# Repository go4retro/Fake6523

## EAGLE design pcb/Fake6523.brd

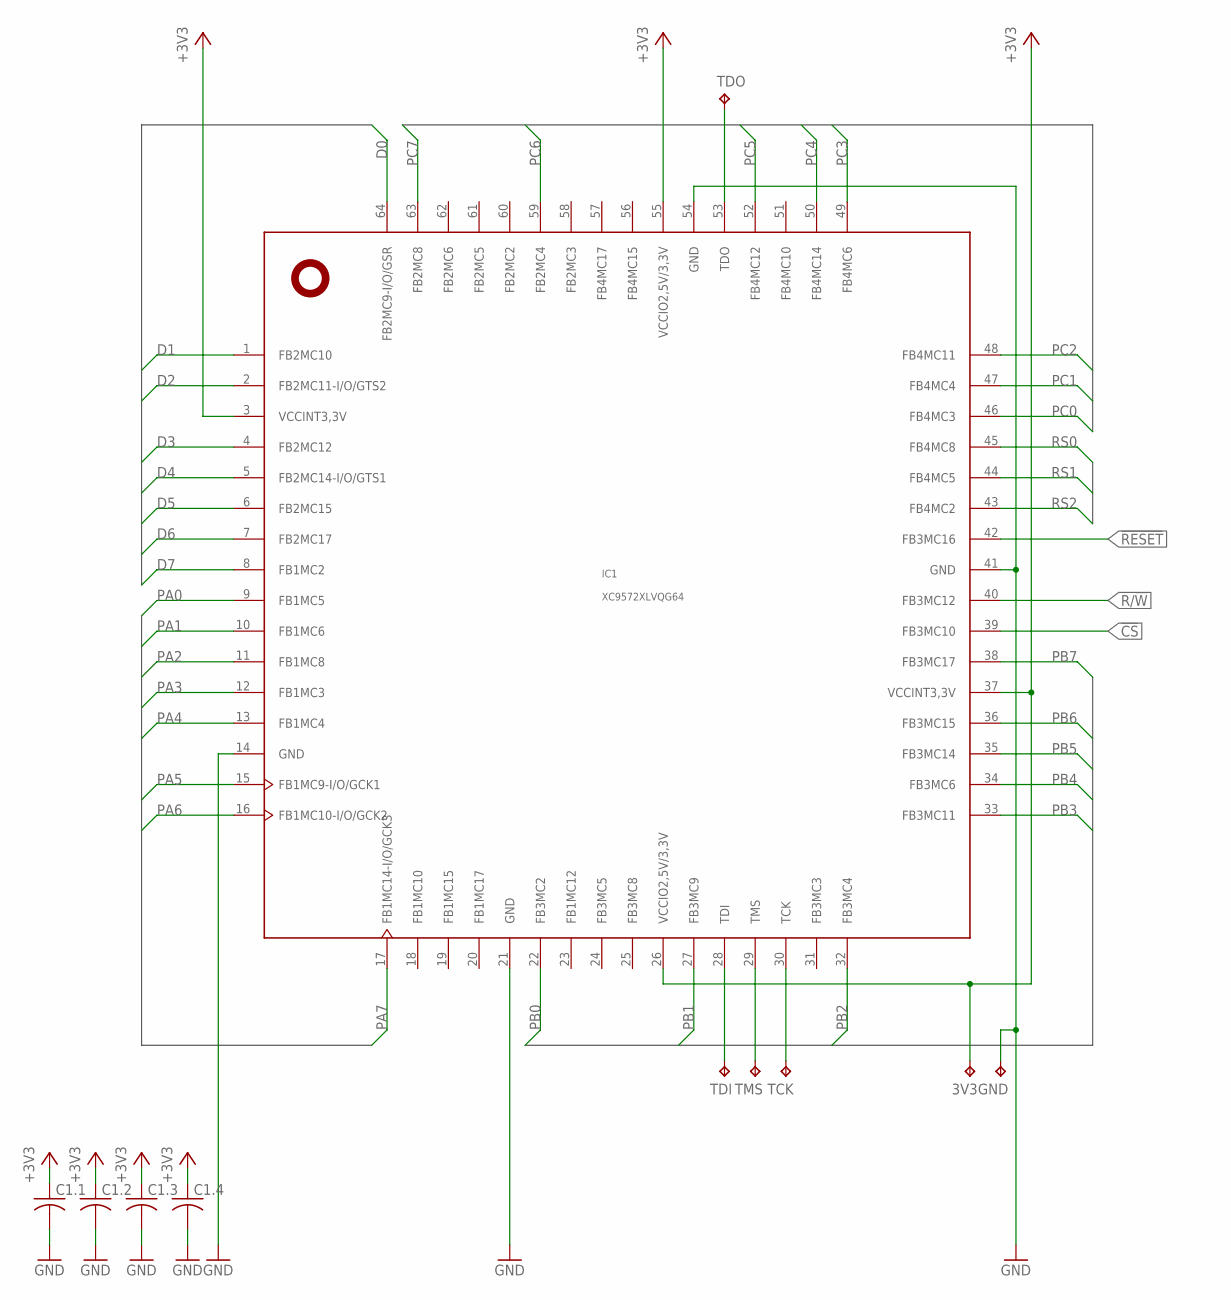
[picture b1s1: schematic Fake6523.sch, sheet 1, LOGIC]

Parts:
3V3: TPTP08R; TP08R
C1.1, C1.2, C1.3, C1.4: C-USC0402; C0402
GND: TPTP08R; TP08R
IC1: XC9572XLVQG64; VQFP64
TCK: TPTP08R; TP08R
TDI: TPTP08R; TP08R
TDO: TPTP08R; TP08R
TMS: TPTP08R; TP08R

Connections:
!CS: IC1.39 (FB3MC10); also elsewhere on the board
!RESET: IC1.42 (FB3MC16); also elsewhere on the board
+3V3: 3V3.TP, C1.1.1, C1.2.1, C1.3.1, C1.4.1, IC1.3 (VCCINT3,3V), IC1.26 (VCCIO2,5V/3,3V), IC1.37 (VCCINT3,3V), IC1.55 (VCCIO2,5V/3,3V); also elsewhere on the board
D0: IC1.64 (FB2MC9-I/O/GSR); also elsewhere on the board
D1: IC1.1 (FB2MC10); also elsewhere on the board
D2: IC1.2 (FB2MC11-I/O/GTS2); also elsewhere on the board
D3: IC1.4 (FB2MC12); also elsewhere on the board
D4: IC1.5 (FB2MC14-I/O/GTS1); also elsewhere on the board
D5: IC1.6 (FB2MC15); also elsewhere on the board
D6: IC1.7 (FB2MC17); also elsewhere on the board
D7: IC1.8 (FB1MC2); also elsewhere on the board
GND: C1.1.2, C1.2.2, C1.3.2, C1.4.2, GND.TP, IC1.14 (GND), IC1.21 (GND), IC1.41 (GND), IC1.54 (GND); also elsewhere on the board
PA0: IC1.9 (FB1MC5); also elsewhere on the board
PA1: IC1.10 (FB1MC6); also elsewhere on the board
PA2: IC1.11 (FB1MC8); also elsewhere on the board
PA3: IC1.12 (FB1MC3); also elsewhere on the board
PA4: IC1.13 (FB1MC4); also elsewhere on the board
PA5: IC1.15 (FB1MC9-I/O/GCK1); also elsewhere on the board
PA6: IC1.16 (FB1MC10-I/O/GCK2); also elsewhere on the board
PA7: IC1.17 (FB1MC14-I/O/GCK3); also elsewhere on the board
PB0: IC1.22 (FB3MC2); also elsewhere on the board
PB1: IC1.27 (FB3MC9); also elsewhere on the board
PB2: IC1.32 (FB3MC4); also elsewhere on the board
PB3: IC1.33 (FB3MC11); also elsewhere on the board
PB4: IC1.34 (FB3MC6); also elsewhere on the board
PB5: IC1.35 (FB3MC14); also elsewhere on the board
PB6: IC1.36 (FB3MC15); also elsewhere on the board
PB7: IC1.38 (FB3MC17); also elsewhere on the board
PC0: IC1.46 (FB4MC3); also elsewhere on the board
PC1: IC1.47 (FB4MC4); also elsewhere on the board
PC2: IC1.48 (FB4MC11); also elsewhere on the board
PC3: IC1.49 (FB4MC6); also elsewhere on the board
PC4: IC1.50 (FB4MC14); also elsewhere on the board
PC5: IC1.52 (FB4MC12); also elsewhere on the board
PC6: IC1.59 (FB2MC4); also elsewhere on the board
PC7: IC1.63 (FB2MC8); also elsewhere on the board
R/!W: IC1.40 (FB3MC12); also elsewhere on the board
RS0: IC1.45 (FB4MC8); also elsewhere on the board
RS1: IC1.44 (FB4MC5); also elsewhere on the board
RS2: IC1.43 (FB4MC2); also elsewhere on the board
TCK: IC1.30 (TCK), TCK.TP
TDI: IC1.28 (TDI), TDI.TP
TDO: IC1.53 (TDO), TDO.TP
TMS: IC1.29 (TMS), TMS.TP

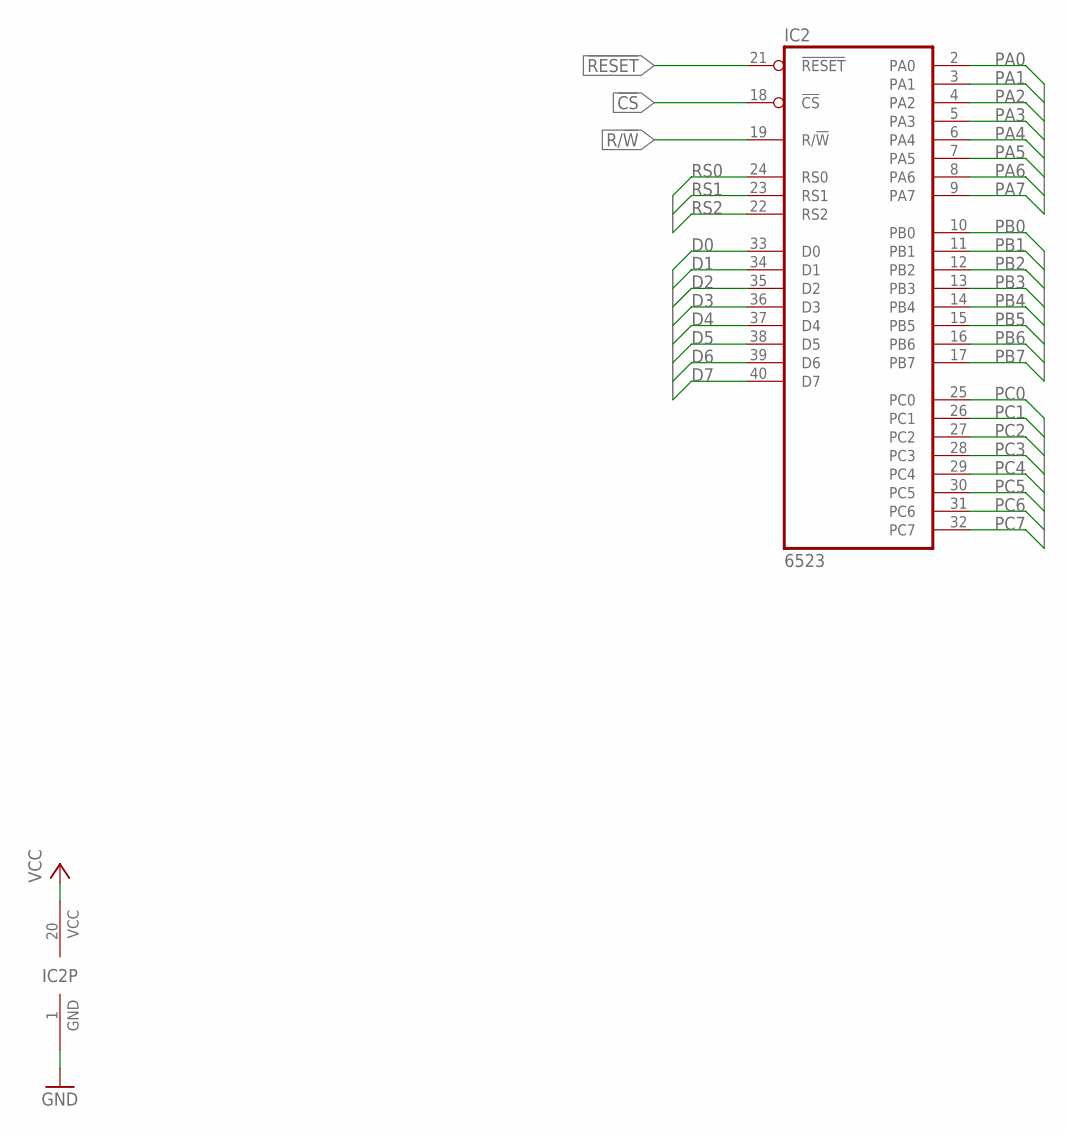
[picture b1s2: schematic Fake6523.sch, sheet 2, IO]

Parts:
IC2: 6523; DIL40-ROUNDPAD

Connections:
!CS: IC2.18 (!CS); also elsewhere on the board
!RESET: IC2.21 (!RESET); also elsewhere on the board
D0: IC2.33 (D0); also elsewhere on the board
D1: IC2.34 (D1); also elsewhere on the board
D2: IC2.35 (D2); also elsewhere on the board
D3: IC2.36 (D3); also elsewhere on the board
D4: IC2.37 (D4); also elsewhere on the board
D5: IC2.38 (D5); also elsewhere on the board
D6: IC2.39 (D6); also elsewhere on the board
D7: IC2.40 (D7); also elsewhere on the board
GND: IC2.1 (GND); also elsewhere on the board
PA0: IC2.2 (PA0); also elsewhere on the board
PA1: IC2.3 (PA1); also elsewhere on the board
PA2: IC2.4 (PA2); also elsewhere on the board
PA3: IC2.5 (PA3); also elsewhere on the board
PA4: IC2.6 (PA4); also elsewhere on the board
PA5: IC2.7 (PA5); also elsewhere on the board
PA6: IC2.8 (PA6); also elsewhere on the board
PA7: IC2.9 (PA7); also elsewhere on the board
PB0: IC2.10 (PB0); also elsewhere on the board
PB1: IC2.11 (PB1); also elsewhere on the board
PB2: IC2.12 (PB2); also elsewhere on the board
PB3: IC2.13 (PB3); also elsewhere on the board
PB4: IC2.14 (PB4); also elsewhere on the board
PB5: IC2.15 (PB5); also elsewhere on the board
PB6: IC2.16 (PB6); also elsewhere on the board
PB7: IC2.17 (PB7); also elsewhere on the board
PC0: IC2.25 (PC0); also elsewhere on the board
PC1: IC2.26 (PC1); also elsewhere on the board
PC2: IC2.27 (PC2); also elsewhere on the board
PC3: IC2.28 (PC3); also elsewhere on the board
PC4: IC2.29 (PC4); also elsewhere on the board
PC5: IC2.30 (PC5); also elsewhere on the board
PC6: IC2.31 (PC6); also elsewhere on the board
PC7: IC2.32 (PC7); also elsewhere on the board
R/!W: IC2.19 (R/!W); also elsewhere on the board
RS0: IC2.24 (RS0); also elsewhere on the board
RS1: IC2.23 (RS1); also elsewhere on the board
RS2: IC2.22 (RS2); also elsewhere on the board
VCC: IC2.20 (VCC); also elsewhere on the board

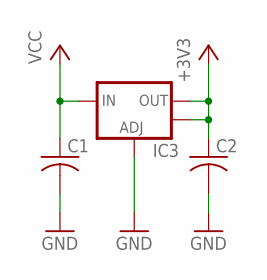
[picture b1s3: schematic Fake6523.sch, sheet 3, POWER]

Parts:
C1, C2: C-USC0805; C0805
IC3: V_REG_LM1117SOT223; SOT223

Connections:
+3V3: C2.1, IC3.2 (OUT), IC3.4 (OUT); also elsewhere on the board
GND: C1.2, C2.2, IC3.1 (ADJ); also elsewhere on the board
VCC: C1.1, IC3.3 (IN); also elsewhere on the board

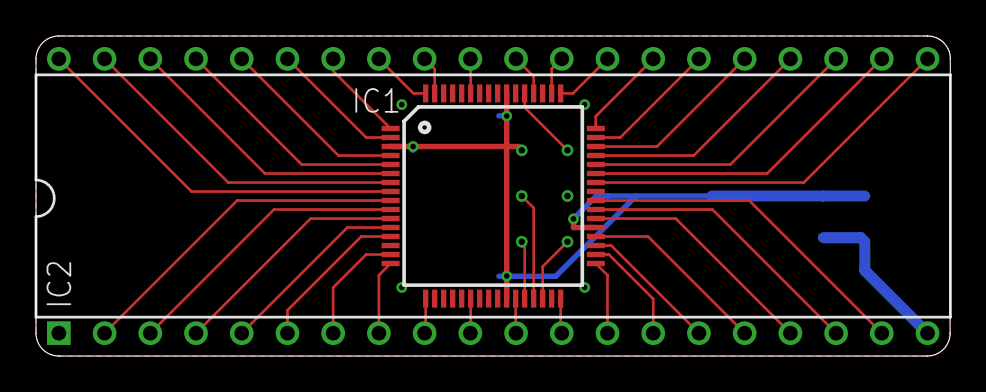
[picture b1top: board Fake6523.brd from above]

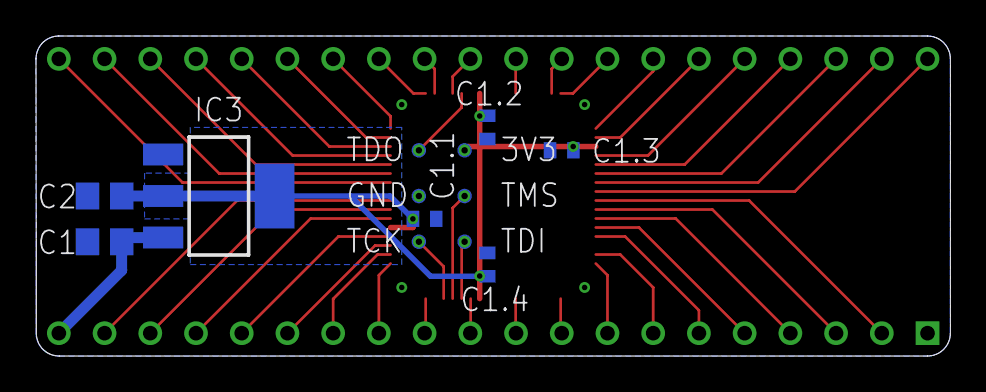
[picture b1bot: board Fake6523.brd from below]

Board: 2 copper layers, 50.8 x 17.8 mm, 15 parts (13 on the bottom side), 45 nets.

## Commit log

2019-01-21 Forgot a file
2019-01-21 Added UCF file and fixed lack of clock signal.
2020-07-25 Add files via upload
    Added missing programming file

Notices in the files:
parts and their libraries:
SparkFun: Licensing: CC v3.0 Share-Alike You are welcome to use this library for commercial purposes.
